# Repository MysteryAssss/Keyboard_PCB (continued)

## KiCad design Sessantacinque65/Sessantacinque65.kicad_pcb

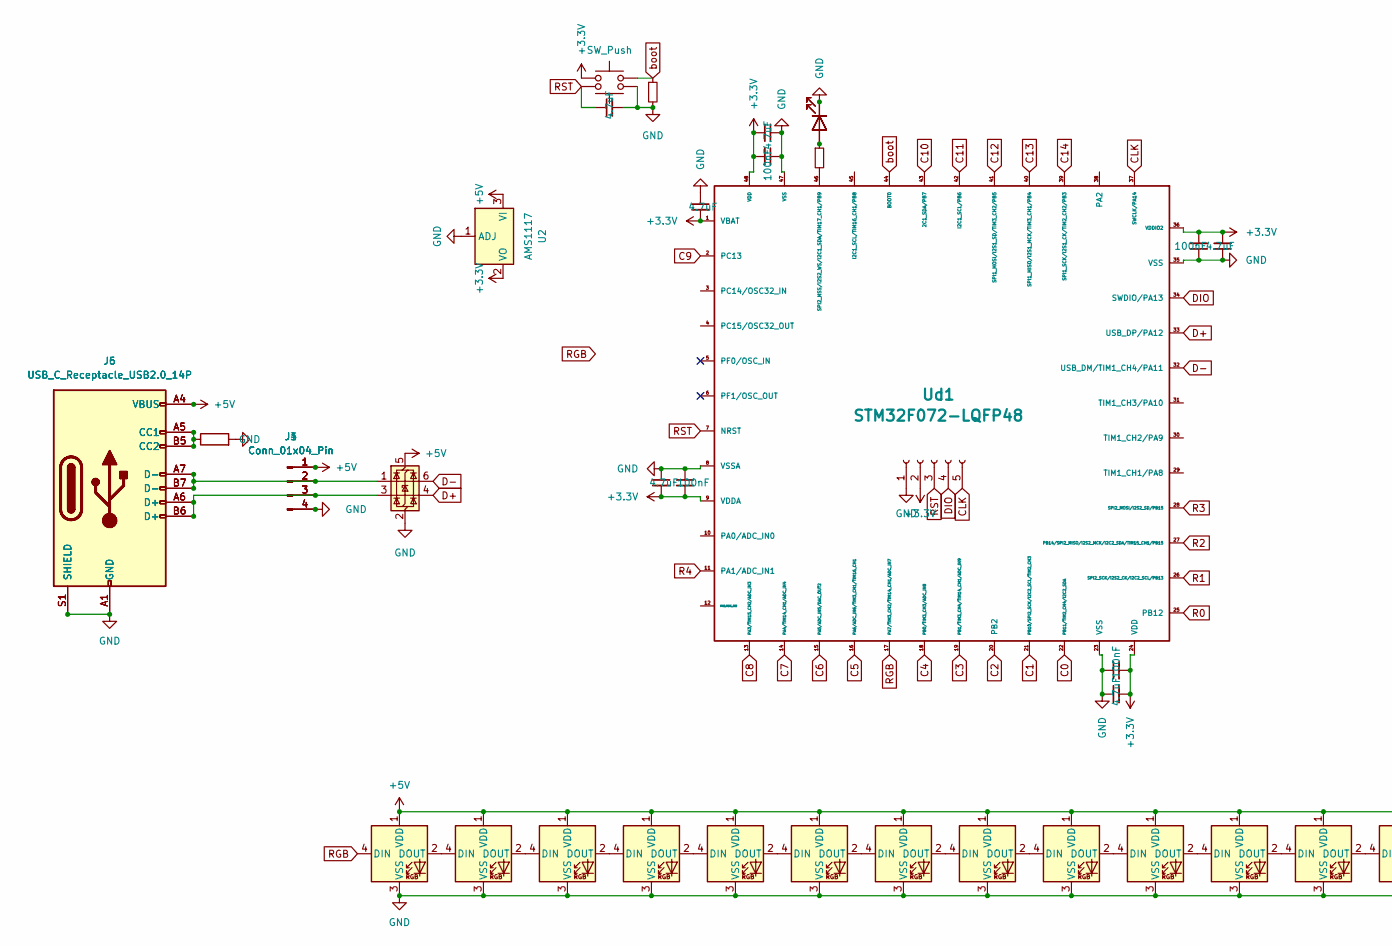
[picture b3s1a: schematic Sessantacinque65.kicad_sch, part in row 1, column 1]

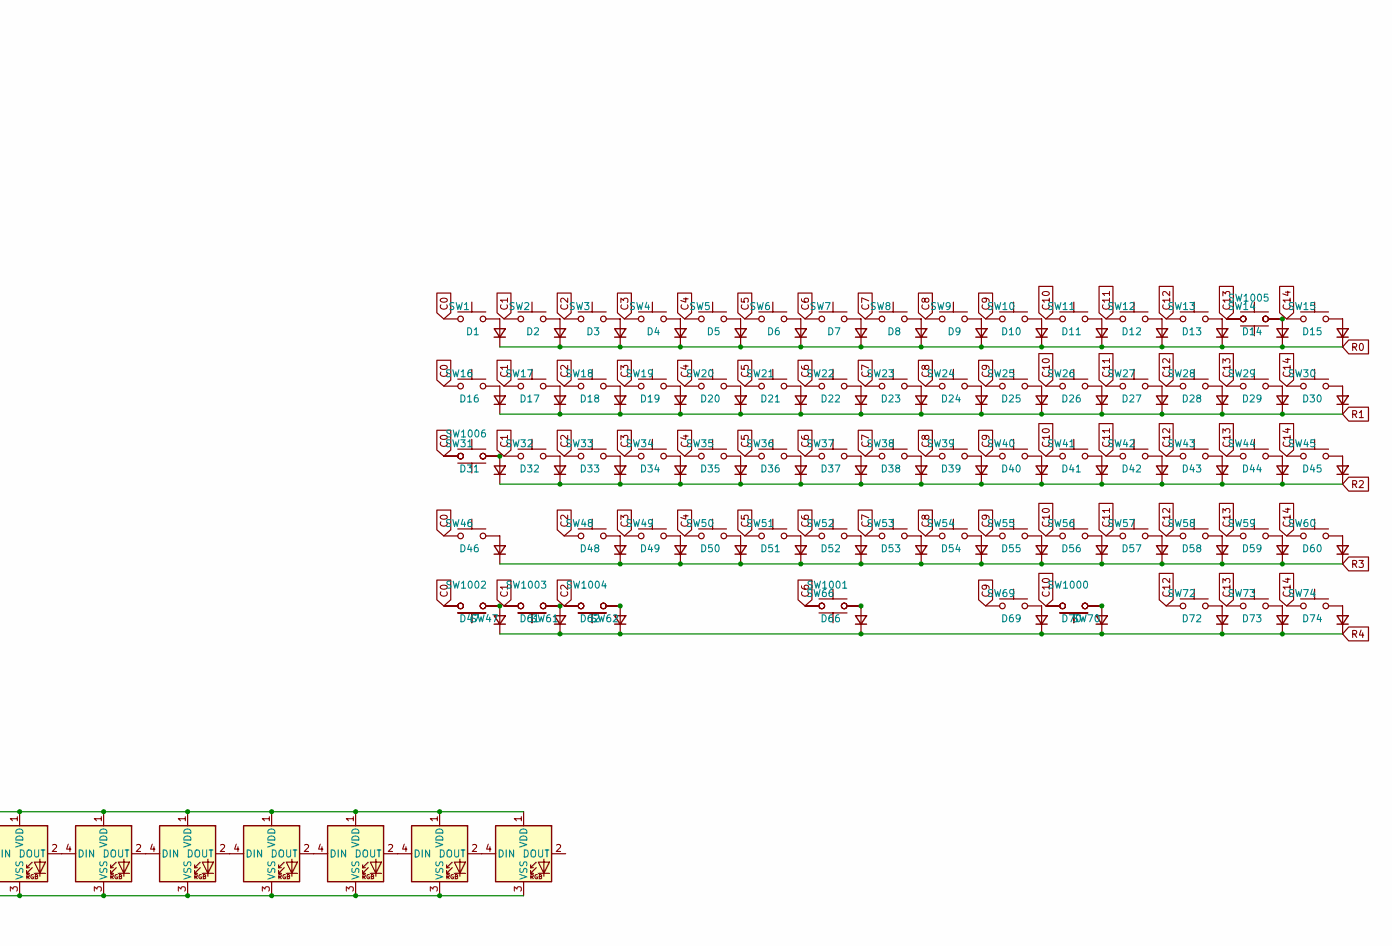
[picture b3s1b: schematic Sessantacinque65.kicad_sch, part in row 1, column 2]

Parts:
C1, C3, C5, C7: 100nF; C_0805_2012Metric
C2, C4, C6, C8, C9, C10: 4.7uF; C_0805_2012Metric
D1, D2, D3, D4, D5, D6, D7, D8, D9, D10, D11, D12, D13, D14, D15, D16, D17, D18, D19, D20, D21, D22, D23, D24, D25, D26, D27, D28, D29, D30, D31, D32, D33, D34, D35, D36, D37, D38, D39, D40, D41, D42, D43, D44, D45, D46, D47, D48, D49, D50, D51, D52, D53, D54, D55, D56, D57, D58, D59, D60, D61, D62, D66, D69, D70, D72, D73, D74: D_Small; D_MiniMELF
DRGB1, DRGB2, DRGB3, DRGB4, DRGB5, DRGB6, DRGB7, DRGB8, DRGB9, DRGB10, DRGB11, DRGB12, DRGB13, DRGB14, DRGB15, DRGB16, DRGB17, DRGB20: WS2812B; LED_WS2812B_PLCC4_5.0x5.0mm_P3.2mm
Dled1, Dled2: LED; LED-6028
J1, J3, J4: Conn_01x04_Pin; JST_SH_SM04B-SRSS-TB_1x04-1MP_P1.00mm_Horizontal
J2: Conn_01x05_Socket; JST_PH_B5B-PH-K_1x05_P2.00mm_Vertical
J5, J6: USB_C_Receptacle_USB2.0_14P; USB_C_Receptacle_HRO_TYPE-C-31-M-12
R1, R3: R_Small; R_0805_2012Metric
R2: R; R_0805_2012Metric
SW1, SW2, SW3, SW4, SW5, SW6, SW7, SW8, SW9, SW10, SW11, SW12, SW13, SW14, SW15, SW17, SW18, SW19, SW20, SW21, SW22, SW23, SW24, SW25, SW26, SW27, SW28, SW30, SW32, SW33, SW34, SW35, SW36, SW37, SW38, SW39, SW40, SW41, SW42, SW43, SW45, SW48, SW49, SW50, SW51, SW52, SW53, SW54, SW55, SW56, SW57, SW59, SW60, SW72, SW73, SW74, SW1003, SW1005: SW_Push; MXOnly-1U_N
SW16, SW29, SW1000, SW1002, SW1004: SW_Push; MXOnly-1.5U_N
SW31, SW58: SW_Push; MXOnly-1.75U_N
SW44, SW46: SW_Push; MXOnly-2.25U_N
SW47, SW61, SW62, SW69, SW70, SW1006: SW_Push; MXOnly-1.25U_N
SW66: SW_Push; MXOnly-6.25U-FLIPPED-ReversedStabilizers_N
SW1001: SW_Push; MXOnly-7U-ReversedStabilizers_N
SWbôt1: SW_Push; JST_EH_B2B-EH-A_1x02_P2.50mm_Vertical
SWbôtrst1: SW_Push; JST_EH_B2B-EH-A_1x02_P2.50mm_Vertical
U2: AMS1117; SOT-223-3_TabPin2
U3: USBLC6-2SC6; SOT-23-6
Ud1: STM32F072-LQFP48; LQFP-48_7x7mm_P0.5mm

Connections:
+3.3V: C1.2, C2.2, C3.2, C4.2, C5.2, C6.2, C7.2, C8.2, C9.2, J2.2, SWbôt1.1, U2.2 (VO), Ud1.1 (VBAT), Ud1.9 (VDDA), Ud1.24 (VDD), Ud1.36 (VDDIO2), Ud1.48 (VDD)
+5V: DRGB1.1 (VDD), DRGB2.1 (VDD), DRGB3.1 (VDD), DRGB4.1 (VDD), DRGB5.1 (VDD), DRGB6.1 (VDD), DRGB7.1 (VDD), DRGB8.1 (VDD), DRGB9.1 (VDD), DRGB10.1 (VDD), DRGB11.1 (VDD), DRGB12.1 (VDD), DRGB13.1 (VDD), DRGB14.1 (VDD), DRGB15.1 (VDD), DRGB16.1 (VDD), DRGB17.1 (VDD), DRGB20.1 (VDD), J1.1, J3.1, J4.1, J5.A4 (VBUS), J5.A9 (VBUS), J5.B4 (VBUS), J5.B9 (VBUS), J6.A4 (VBUS), J6.A9 (VBUS), J6.B4 (VBUS), J6.B9 (VBUS), U2.3 (VI), U3.5 (VBUS)
C0: SW1.1, SW16.1, SW31.1, SW46.1, SW47.2, SW1002.2, SW1006.2, Ud1.22 (PB11/TIM2_CH4/I2C2_SDA)
C1: SW2.1, SW17.1, SW32.1, SW61.2, SW1003.2, Ud1.21 (PB10/SPI2_SCK/I2C2_SCL/TIM2_CH3)
C2: SW3.1, SW18.1, SW33.1, SW48.1, SW62.2, SW1004.2, Ud1.20 (PB2)
C3: SW4.1, SW19.1, SW34.1, SW49.1, Ud1.19 (PB1/TIM3_CH4/TIM14_CH1/ADC_IN9)
C4: SW5.1, SW20.1, SW35.1, SW50.1, Ud1.18 (PB0/TIM3_CH3/ADC_IN8)
C5: SW6.1, SW21.1, SW36.1, SW51.1, Ud1.16 (PA6/ADC_IN6/TIM3_CH1/TIM16_CH1)
C6: SW7.1, SW22.1, SW37.1, SW52.1, SW66.1, SW1001.2, Ud1.15 (PA5/ADC_IN5/DAC_OUT2)
C7: SW8.1, SW23.1, SW38.1, SW53.1, Ud1.14 (PA4/TIM14_CH1/ADC_IN4)
C8: SW9.1, SW24.1, SW39.1, SW54.1, Ud1.13 (PA3/TIM15_CH2/ADC_IN3)
C9: SW10.1, SW25.1, SW40.1, SW55.1, SW69.1, Ud1.2 (PC13)
C10: SW11.1, SW26.1, SW41.1, SW56.1, SW70.2, SW1000.2, Ud1.43 (2C1_SDA/PB7)
C11: SW12.1, SW27.1, SW42.1, SW57.1, Ud1.42 (I2C1_SCL/PB6)
C12: SW13.1, SW28.1, SW43.1, SW58.1, SW72.1, Ud1.41 (SPI1_MOSI/I2S1_SD/TIM3_CH2/PB5)
C13: SW14.1, SW29.1, SW44.1, SW59.1, SW73.1, SW1005.2, Ud1.40 (SPI1_MISO/I2S1_MCK/TIM3_CH1/PB4)
C14: SW15.1, SW30.1, SW45.1, SW60.1, SW74.1, Ud1.39 (SPI1_SCK/I2S1_CK/TIM2_CH2/PB3)
CLK: J2.5, Ud1.37 (SWCLK/PA14)
D+: U3.4 (I/O2), Ud1.33 (USB_DP/PA12)
D-: U3.6 (I/O1), Ud1.32 (USB_DM/TIM1_CH4/PA11)
DIO: J2.4, Ud1.34 (SWDIO/PA13)
GND: C1.1, C2.1, C3.1, C4.1, C5.1, C6.1, C7.1, C8.1, C9.1, C10.2, DRGB1.3 (VSS), DRGB2.3 (VSS), DRGB3.3 (VSS), DRGB4.3 (VSS), DRGB5.3 (VSS), DRGB6.3 (VSS), DRGB7.3 (VSS), DRGB8.3 (VSS), DRGB9.3 (VSS), DRGB10.3 (VSS), DRGB11.3 (VSS), DRGB12.3 (VSS), DRGB13.3 (VSS), DRGB14.3 (VSS), DRGB15.3 (VSS), DRGB16.3 (VSS), DRGB17.3 (VSS), DRGB20.3 (VSS), Dled1.1 (K), Dled2.1 (K), J1.4, J2.1, J3.4, J4.4, J5.A1 (GND), J5.A12 (GND), J5.B1 (GND), J5.B12 (GND), J5.S1 (SHIELD), J6.A1 (GND), J6.A12 (GND), J6.B1 (GND), J6.B12 (GND), J6.S1 (SHIELD), R1.2, R2.2, SWbôtrst1.1, U2.1 (ADJ), U3.2 (GND), Ud1.8 (VSSA), Ud1.23 (VSS), Ud1.35 (VSS), Ud1.47 (VSS)
unnamed: D1.2 (A), SW1.2
unnamed: D2.2 (A), SW2.2
unnamed: D3.2 (A), SW3.2
unnamed: D4.2 (A), SW4.2
unnamed: D5.2 (A), SW5.2
unnamed: D6.2 (A), SW6.2
unnamed: D7.2 (A), SW7.2
unnamed: D8.2 (A), SW8.2
unnamed: D9.2 (A), SW9.2
unnamed: D10.2 (A), SW10.2
unnamed: D11.2 (A), SW11.2
unnamed: D12.2 (A), SW12.2
unnamed: D13.2 (A), SW13.2
unnamed: D14.2 (A), SW14.2, SW1005.1
unnamed: D15.2 (A), SW15.2
unnamed: D16.2 (A), SW16.2
unnamed: D17.2 (A), SW17.2
unnamed: D18.2 (A), SW18.2
unnamed: D19.2 (A), SW19.2
unnamed: D20.2 (A), SW20.2
unnamed: D21.2 (A), SW21.2
unnamed: D22.2 (A), SW22.2
unnamed: D23.2 (A), SW23.2
unnamed: D24.2 (A), SW24.2
unnamed: D25.2 (A), SW25.2
unnamed: D26.2 (A), SW26.2
unnamed: D27.2 (A), SW27.2
unnamed: D28.2 (A), SW28.2
unnamed: D29.2 (A), SW29.2
unnamed: D30.2 (A), SW30.2
unnamed: D31.2 (A), SW31.2, SW1006.1
unnamed: D32.2 (A), SW32.2
unnamed: D33.2 (A), SW33.2
unnamed: D34.2 (A), SW34.2
unnamed: D35.2 (A), SW35.2
unnamed: D36.2 (A), SW36.2
unnamed: D37.2 (A), SW37.2
unnamed: D38.2 (A), SW38.2
unnamed: D39.2 (A), SW39.2
unnamed: D40.2 (A), SW40.2
unnamed: D41.2 (A), SW41.2
unnamed: D42.2 (A), SW42.2
unnamed: D43.2 (A), SW43.2
unnamed: D44.2 (A), SW44.2
unnamed: D45.2 (A), SW45.2
unnamed: D46.2 (A), SW46.2
unnamed: D47.2 (A), SW47.1, SW1002.1
unnamed: D48.2 (A), SW48.2
unnamed: D49.2 (A), SW49.2
unnamed: D50.2 (A), SW50.2
unnamed: D51.2 (A), SW51.2
unnamed: D52.2 (A), SW52.2
unnamed: D53.2 (A), SW53.2
unnamed: D54.2 (A), SW54.2
unnamed: D55.2 (A), SW55.2
unnamed: D56.2 (A), SW56.2
unnamed: D57.2 (A), SW57.2
unnamed: D58.2 (A), SW58.2
unnamed: D59.2 (A), SW59.2
unnamed: D60.2 (A), SW60.2
unnamed: D61.2 (A), SW61.1, SW1003.1
unnamed: D62.2 (A), SW62.1, SW1004.1
unnamed: D66.2 (A), SW66.2, SW1001.1
unnamed: D69.2 (A), SW69.2
unnamed: D70.2 (A), SW70.1, SW1000.1
unnamed: D72.2 (A), SW72.2
unnamed: D73.2 (A), SW73.2
unnamed: D74.2 (A), SW74.2
unnamed: DRGB1.4 (DIN), DRGB20.2 (DOUT)
unnamed: DRGB1.2 (DOUT), DRGB2.4 (DIN)
unnamed: DRGB2.2 (DOUT), DRGB3.4 (DIN)
unnamed: DRGB3.2 (DOUT), DRGB4.4 (DIN)
unnamed: DRGB4.2 (DOUT), DRGB5.4 (DIN)
unnamed: DRGB5.2 (DOUT), DRGB6.4 (DIN)
unnamed: DRGB6.2 (DOUT), DRGB7.4 (DIN)
unnamed: DRGB7.2 (DOUT), DRGB8.4 (DIN)
unnamed: DRGB8.2 (DOUT), DRGB9.4 (DIN)
unnamed: DRGB9.2 (DOUT), DRGB10.4 (DIN)
unnamed: DRGB10.2 (DOUT), DRGB11.4 (DIN)
unnamed: DRGB11.2 (DOUT), DRGB12.4 (DIN)
unnamed: DRGB12.2 (DOUT), DRGB13.4 (DIN)
unnamed: DRGB13.2 (DOUT), DRGB14.4 (DIN)
unnamed: DRGB14.2 (DOUT), DRGB15.4 (DIN)
unnamed: DRGB15.2 (DOUT), DRGB16.4 (DIN)
unnamed: DRGB16.2 (DOUT), DRGB17.4 (DIN)
unnamed: Dled1.2 (A), Dled2.2 (A), R3.1
unnamed: J1.2, J3.2, J4.2, J5.A7 (D-), J5.B7 (D-), J6.A7 (D-), J6.B7 (D-), U3.1 (I/O1)
unnamed: J1.3, J3.3, J4.3, J5.A6 (D+), J5.B6 (D+), J6.A6 (D+), J6.B6 (D+), U3.3 (I/O2)
unnamed: J5.A5 (CC1), J5.B5 (CC2), J6.A5 (CC1), J6.B5 (CC2), R2.1
unnamed: R3.2, Ud1.46 (SPI2_NSS/I2S2_WS/I2C1_SDA/TIM17_CH1/PB9)
R0: D1.1 (K), D2.1 (K), D3.1 (K), D4.1 (K), D5.1 (K), D6.1 (K), D7.1 (K), D8.1 (K), D9.1 (K), D10.1 (K), D11.1 (K), D12.1 (K), D13.1 (K), D14.1 (K), D15.1 (K), Ud1.25 (PB12)
R1: D16.1 (K), D17.1 (K), D18.1 (K), D19.1 (K), D20.1 (K), D21.1 (K), D22.1 (K), D23.1 (K), D24.1 (K), D25.1 (K), D26.1 (K), D27.1 (K), D28.1 (K), D29.1 (K), D30.1 (K), Ud1.26 (SPI2_SCK/I2S2_CK/I2C2_SCL/PB13)
R2: D31.1 (K), D32.1 (K), D33.1 (K), D34.1 (K), D35.1 (K), D36.1 (K), D37.1 (K), D38.1 (K), D39.1 (K), D40.1 (K), D41.1 (K), D42.1 (K), D43.1 (K), D44.1 (K), D45.1 (K), Ud1.27 (PB14/SPI2_MISO/I2S2_MCK/I2C2_SDA/TIM15_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)
R3: D46.1 (K), D48.1 (K), D49.1 (K), D50.1 (K), D51.1 (K), D52.1 (K), D53.1 (K), D54.1 (K), D55.1 (K), D56.1 (K), D57.1 (K), D58.1 (K), D59.1 (K), D60.1 (K), Ud1.28 (SPI2_MOSI/I2S2_SD/PB15)
R4: D47.1 (K), D61.1 (K), D62.1 (K), D66.1 (K), D69.1 (K), D70.1 (K), D72.1 (K), D73.1 (K), D74.1 (K), Ud1.11 (PA1/ADC_IN1)
RGB: DRGB20.4 (DIN), Ud1.17 (PA7/TIM3_CH2/TIM14_CH1/ADC_IN7)
RST: C10.1, J2.3, SWbôtrst1.2, Ud1.7 (NRST)
boot: R1.1, SWbôt1.2, Ud1.44 (BOOT0)

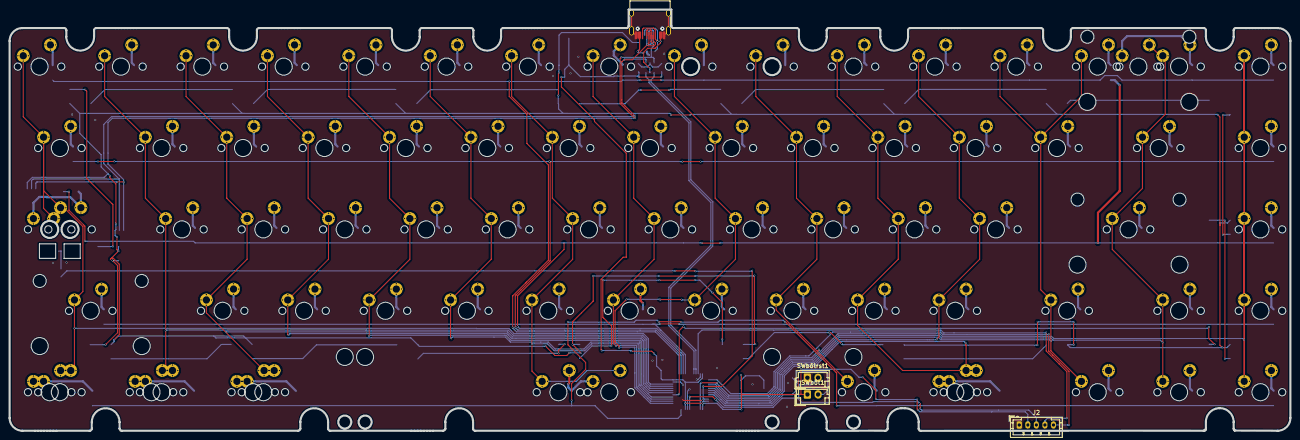
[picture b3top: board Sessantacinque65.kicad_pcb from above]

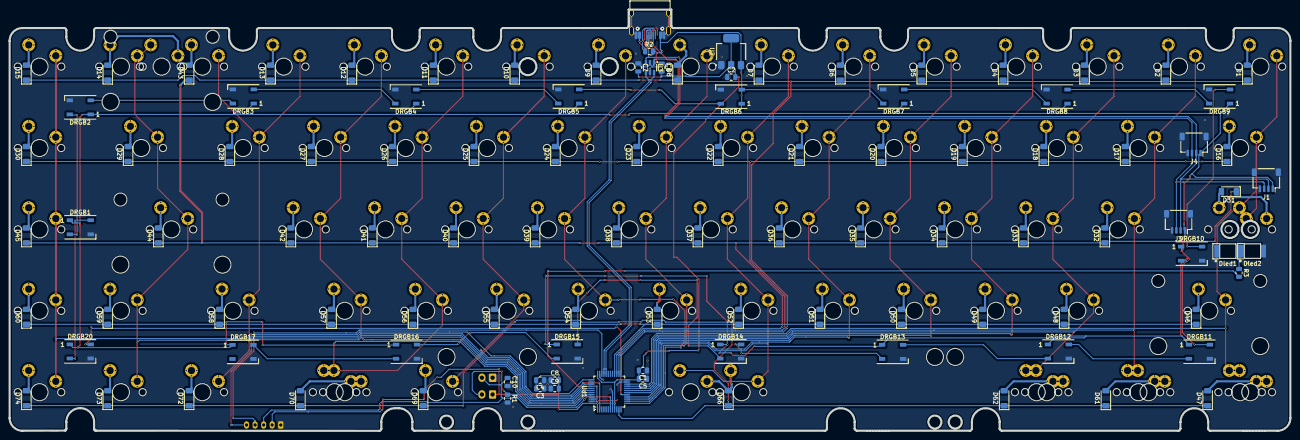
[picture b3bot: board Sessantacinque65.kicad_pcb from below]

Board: 11 copper layers, 299.8 x 98.6 mm, 187 parts (108 on the bottom side), 120 nets.
